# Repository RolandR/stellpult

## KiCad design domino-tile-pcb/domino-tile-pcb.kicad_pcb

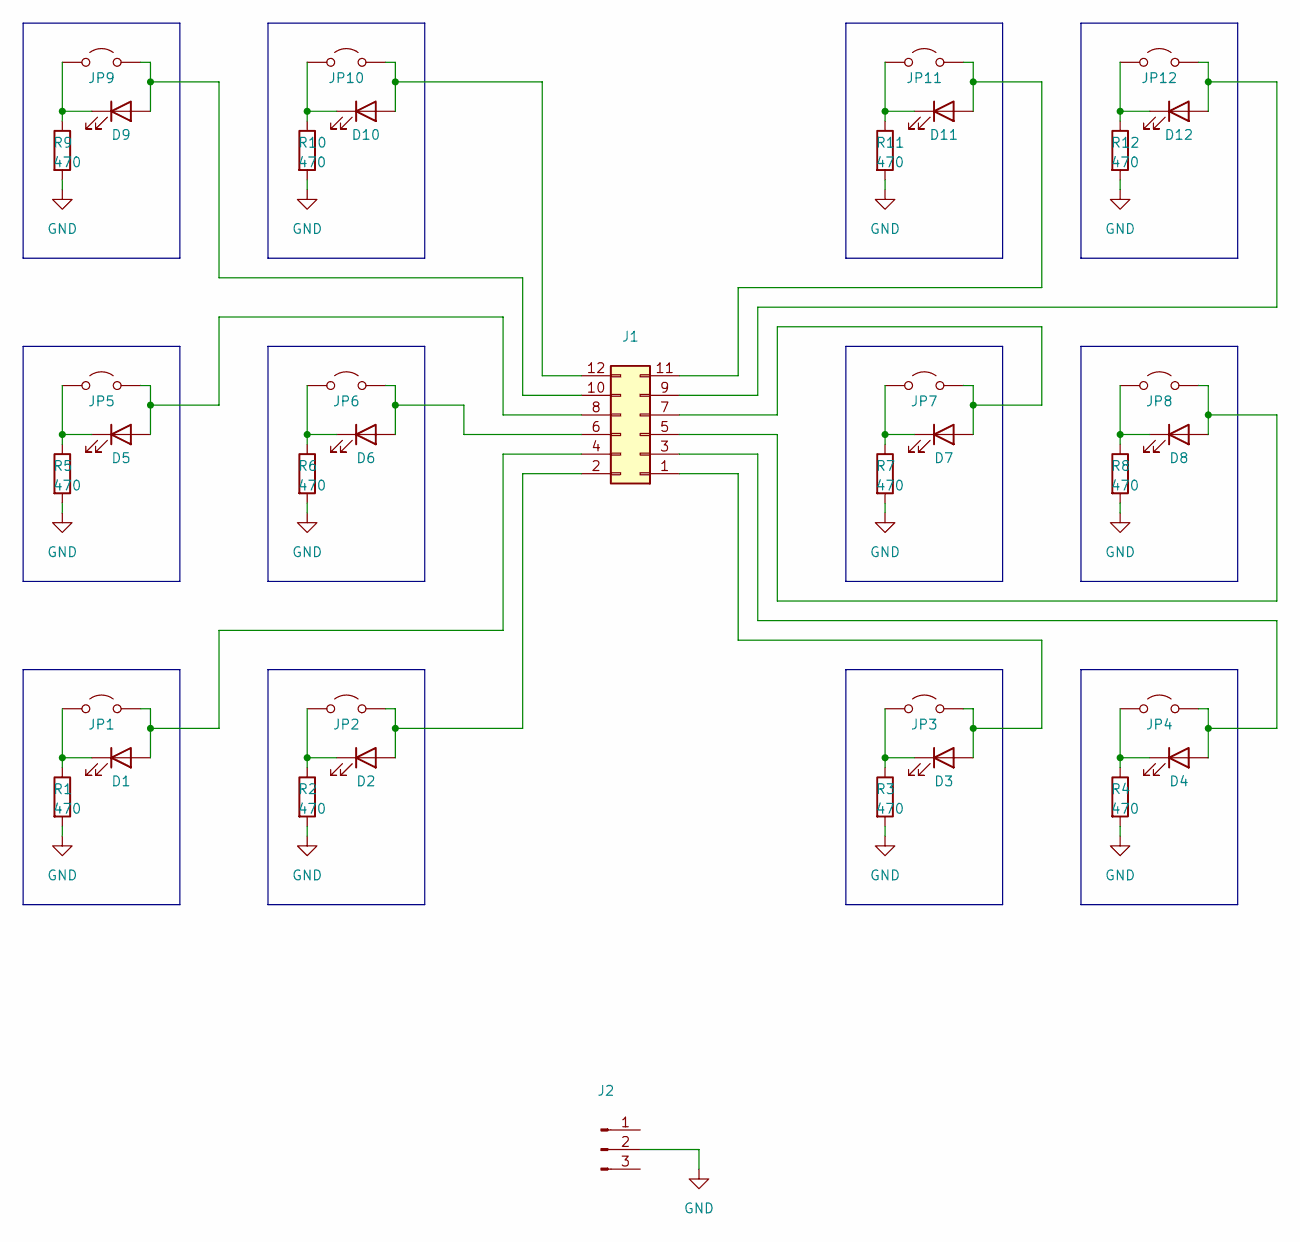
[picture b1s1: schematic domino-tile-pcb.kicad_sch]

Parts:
D1, D2, D3, D4, D5, D6, D7, D8, D9, D10, D11, D12: LED_PLCC_2835_Handsoldering
J1: IDC-Header_2x06_P2.54mm_Vertical_SMD
J2: JST_EH_B3B-EH-A_1x03_P2.50mm_Vertical
JP1, JP2, JP3, JP4, JP5, JP6, JP7, JP8, JP9, JP10, JP11, JP12: SolderJumper-2_P1.3mm_Open_Pad1.0x1.5mm
R1, R2, R3, R4, R5, R6, R7, R8, R9, R10, R11, R12: 470; R_0805_2012Metric_Pad1.20x1.40mm_HandSolder

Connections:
GND: J2.2, R1.2, R2.2, R3.2, R4.2, R5.2, R6.2, R7.2, R8.2, R9.2, R10.2, R11.2, R12.2
unnamed: D1.2 (A), J1.4, JP1.2 (B)
unnamed: D1.1 (K), JP1.1 (A), R1.1
unnamed: D2.2 (A), J1.2, JP2.2 (B)
unnamed: D2.1 (K), JP2.1 (A), R2.1
unnamed: D3.2 (A), J1.1, JP3.2 (B)
unnamed: D3.1 (K), JP3.1 (A), R3.1
unnamed: D4.2 (A), J1.3, JP4.2 (B)
unnamed: D4.1 (K), JP4.1 (A), R4.1
unnamed: D5.2 (A), J1.8, JP5.2 (B)
unnamed: D5.1 (K), JP5.1 (A), R5.1
unnamed: D6.2 (A), J1.6, JP6.2 (B)
unnamed: D6.1 (K), JP6.1 (A), R6.1
unnamed: D7.2 (A), J1.7, JP7.2 (B)
unnamed: D7.1 (K), JP7.1 (A), R7.1
unnamed: D8.2 (A), J1.5, JP8.2 (B)
unnamed: D8.1 (K), JP8.1 (A), R8.1
unnamed: D9.2 (A), J1.10, JP9.2 (B)
unnamed: D9.1 (K), JP9.1 (A), R9.1
unnamed: D10.2 (A), J1.12, JP10.2 (B)
unnamed: D10.1 (K), JP10.1 (A), R10.1
unnamed: D11.2 (A), J1.11, JP11.2 (B)
unnamed: D11.1 (K), JP11.1 (A), R11.1
unnamed: D12.2 (A), J1.9, JP12.2 (B)
unnamed: D12.1 (K), JP12.1 (A), R12.1

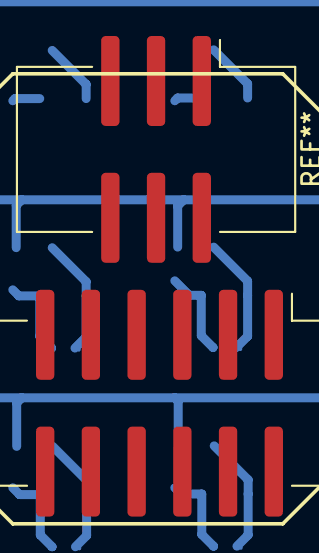
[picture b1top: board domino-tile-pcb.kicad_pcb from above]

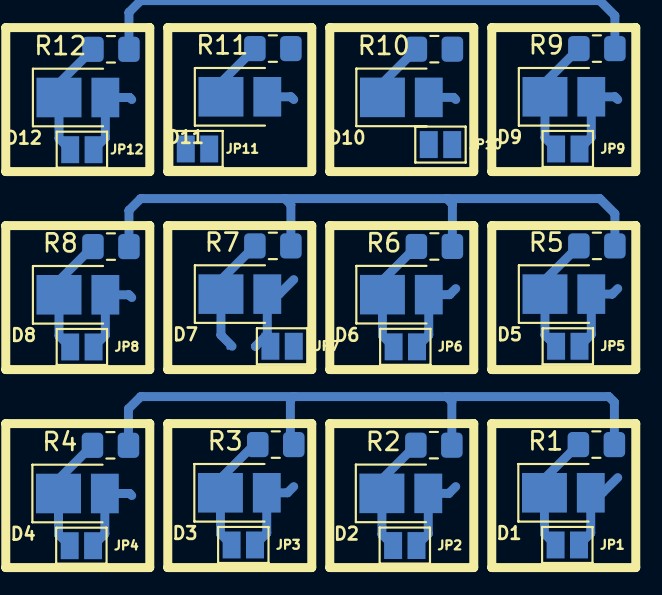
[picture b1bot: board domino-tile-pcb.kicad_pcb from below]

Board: 2 copper layers, 37 parts (36 on the bottom side), 25 nets.

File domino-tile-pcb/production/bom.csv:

Designator,Footprint,Quantity,Value,LCSC Part #
"D1, D10, D11, D12, D2, D3, D4, D5, D6, D7, D8, D9",LED_PLCC_2835_Handsoldering,12,~,
J1,IDC-Header_2x06_P2.54mm_Vertical_SMD,1,~,
"R1, R10, R11, R12, R2, R3, R4, R5, R6, R7, R8, R9",0805,12,470,

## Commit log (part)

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2026-01-10 draw some Domino tiles and layout my control panel
2026-01-16 layout Blausee-Mitholz station
2026-01-17 draw emergency buttons
2026-01-19 draw elements for Zuglenkung and Weichenheizung
2026-01-20 design small station 'Gasel' and make a Verschlusstabelle and such for it
2026-01-21 construct a base for the tiles
2026-01-22 design module socket, start work on a PCB which might not go anywhere
2026-01-24 make blank module
2026-01-29 do a lot of things, I guess
2026-01-30 do more things
2026-02-10 work on button
2026-03-24 uhhh
